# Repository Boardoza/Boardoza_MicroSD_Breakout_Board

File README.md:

# Boardoza MicroSD Breakout Board

The **Boardoza MicroSD Breakout Board** is a compact storage solution that enables microSD card interfacing via **SPI communication protocol**. This breakout board features an integrated **voltage regulator** that converts 5V input to 3.3V operation, ensuring safe and reliable communication with microSD cards while maintaining compatibility with both 3.3V and 5V microcontroller systems.

With its small form factor of **20mm x 40mm**, this module provides an easy way to add mass storage capabilities to embedded projects, data logging applications, and IoT devices. The board is optimized for high-speed data transfer and features **3.3V tolerant SPI pins** for seamless integration.

## [Click here to purchase!](https://www.ozdisan.com/p/gelistirme-kitleri-ve-aksesuarlari-617/boardoza-boardoza-microsd-1202712)

|Front Side|Back Side|
|:---:|:---:|
| | |

---

## Key Features

- **SPI Communication Interface:** Standard SPI protocol for universal microcontroller compatibility.
- **Integrated Voltage Regulation:** Converts 5V input to 3.3V operation for safe microSD card interfacing.
- **3.3V Tolerant I/O:** All SPI pins are 3.3V tolerant, protecting the microSD card from overvoltage.
- **High-Speed Data Transfer:** Optimized for fast read/write operations with microSD cards.
- **Compact Design:** Small 20mm x 40mm form factor for space-constrained applications.
- **Wide Compatibility:** Works with microSD and microSDHC cards up to 32GB.
- **Simple Integration:** Standard SPI pinout for easy connection to Arduino, ESP32, STM32, and other platforms.

---

## Technical Specifications

**Input Voltage:** 5V  
**Voltage Input Type:** 6-pin 2.50mm header  
**Operating Voltage:** 3.3V (regulated)  
**Interface:** SPI (Serial Peripheral Interface)  
**Functions:** MicroSD Card Reader/Writer Module  
**I/O Voltage Level:** 3.3V tolerant  
**Supported Cards:** MicroSD, MicroSDHC (up to 32GB)  
**Operating Temperature:** -40°C ~ +85°C  
**Board Dimensions:** 20mm x 40mm

---

## Board Pinout

### **( J1 ) SPI Communication Pins**

| Pin Number | Pin Name | Description |
|:---:|:---:|---|
| 1 | MISO | Master Input Slave Output (3.3V tolerant) |
| 2 | SCK | Serial Clock (3.3V tolerant) |
| 3 | MOSI | Master Output Slave Input (3.3V tolerant) |
| 4 | CS | Chip Select (3.3V tolerant) |
| 5 | GND | Ground (0V reference) |
| 6 | +5V | Positive voltage input |

---

## Board Dimensions

---

## Step Files

[Boardoza MicroSD.step](./assets/MicroSD%20Step.step)

---

## Datasheet

[MicroSD Breakout Board Datasheet.pdf](./assets/MicroSD%20Datasheet.pdf)

---

## Version History

- V1.0.0 - Initial Release

---

## Support

- If you have any questions or need support, please contact <support@boardoza.com>

---

## License

Shield: [![CC BY-SA 4.0][cc-by-sa-shield]][cc-by-sa]

This work is licensed under a [Creative Commons Attribution-ShareAlike 4.0 International License][cc-by-sa].

[![CC BY-SA 4.0][cc-by-sa-image]][cc-by-sa]

[cc-by-sa]: http://creativecommons.org/licenses/by-sa/4.0/
[cc-by-sa-image]: https://licensebuttons.net/l/by-sa/4.0/88x31.png
[cc-by-sa-shield]: https://img.shields.io/badge/License-CC%20BY--SA%204.0-lightgrey.svg

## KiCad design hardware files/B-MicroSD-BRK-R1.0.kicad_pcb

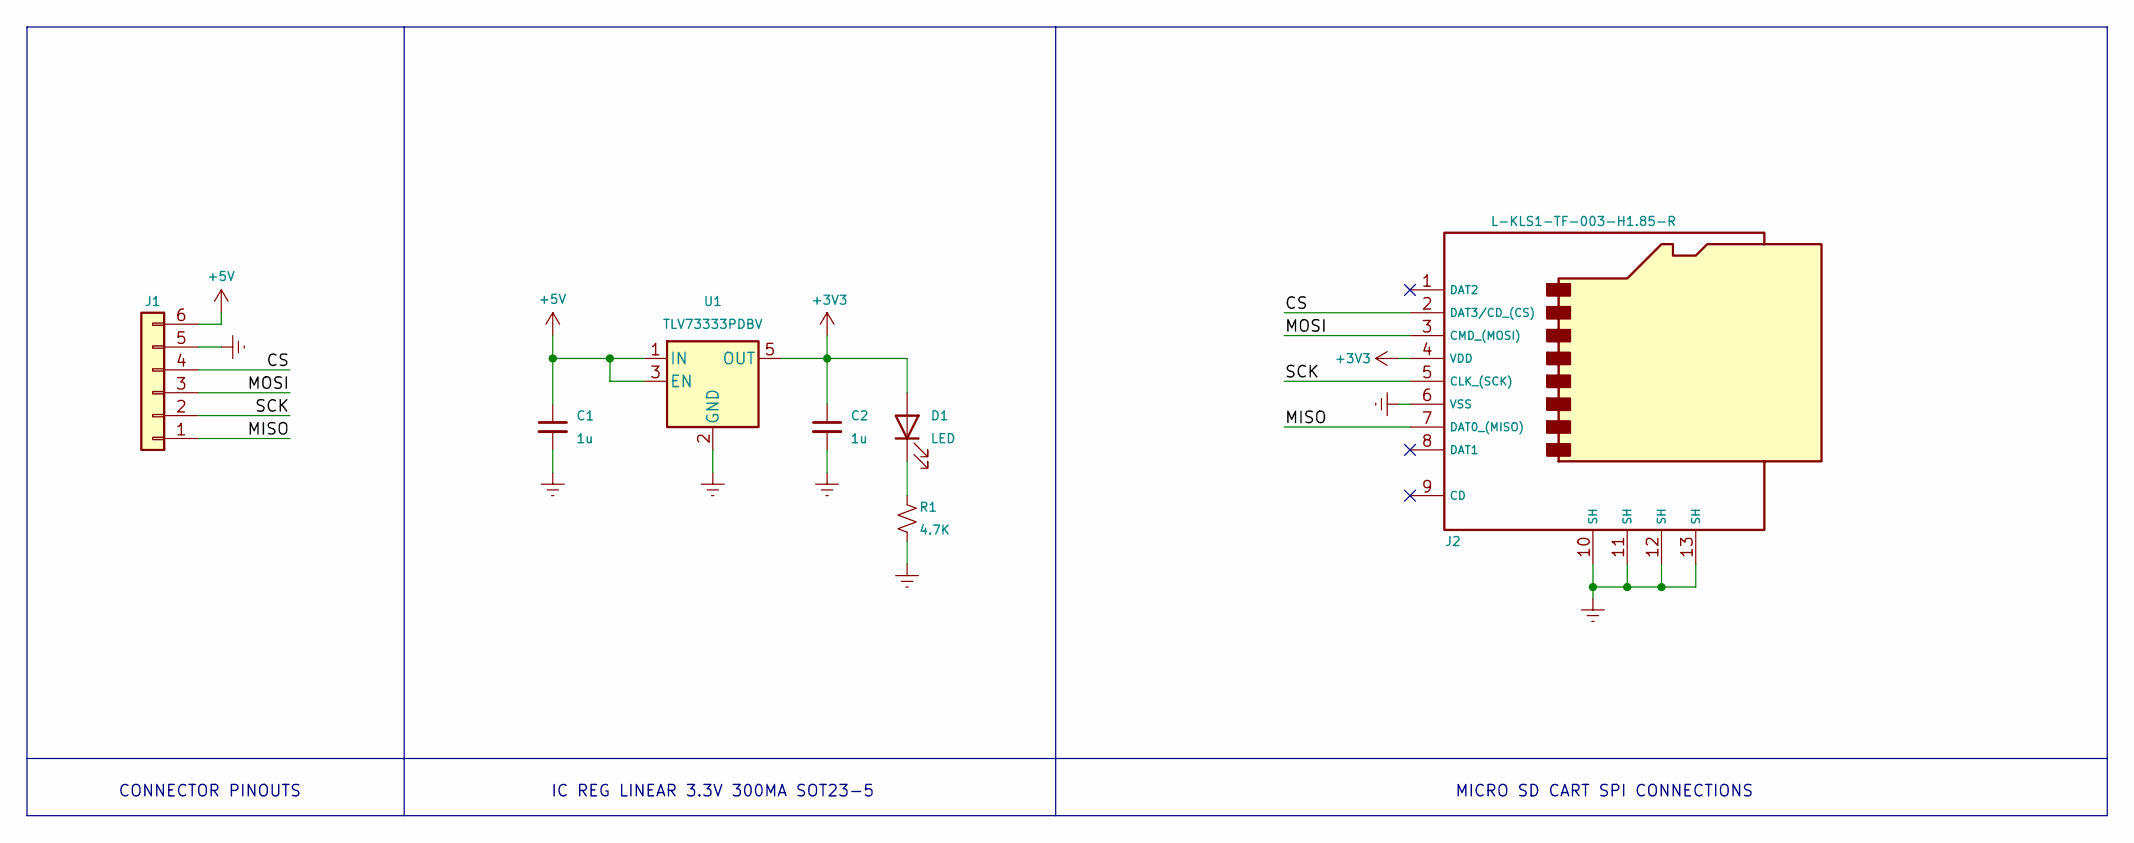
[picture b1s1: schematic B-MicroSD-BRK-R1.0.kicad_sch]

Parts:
C1, C2: 1u; C_0603_1608Metric; MPN CL10B105KA8NNNC
D1: LED; LED_0603_1608Metric; MPN LTST-C190KRKT
J1: Conn_01x06; 2317-06S_1x06_P2.50mm_Vertical; MPN 2317-06S
J2: L-KLS1-TF-003-H1.85-R; MPN L-KLS1-TF-003-H1.85-R
R1: 4.7K; R_0603_1608Metric; MPN 0603SAJ0472T5E
U1: TLV73333PDBV; SOT-23-5; MPN TLV73333PDBVR

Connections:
+3V3: C2.1, D1.2 (A), J2.4 (VDD), U1.5 (OUT)
+5V: C1.1, J1.6, U1.1 (IN), U1.3 (EN)
/CS: J1.4, J2.2 (DAT3/CD_(CS))
/MISO: J1.1, J2.7 (DAT0_(MISO))
/MOSI: J1.3, J2.3 (CMD_(MOSI))
/SCK: J1.2, J2.5 (CLK_(SCK))
Earth: C1.2, C2.2, J1.5, J2.6 (VSS), J2.10 (SH), J2.11 (SH), J2.12 (SH), J2.13 (SH), R1.2, U1.2 (GND)
unnamed: D1.1 (K), R1.1

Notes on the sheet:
CONNECTOR PINOUTS
IC REG LINEAR 3.3V 300MA SOT23-5
MICRO SD CART SPI CONNECTIONS

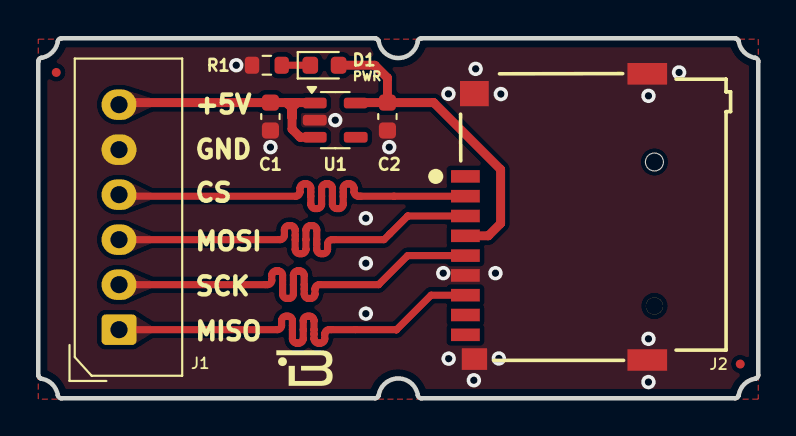
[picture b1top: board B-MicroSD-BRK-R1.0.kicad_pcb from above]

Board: 2 copper layers, 40.0 x 20.0 mm, 7 parts (0 on the bottom side), 8 nets.

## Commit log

2025-11-17 Add MicroSD example
2026-04-29 Fix folder structure
